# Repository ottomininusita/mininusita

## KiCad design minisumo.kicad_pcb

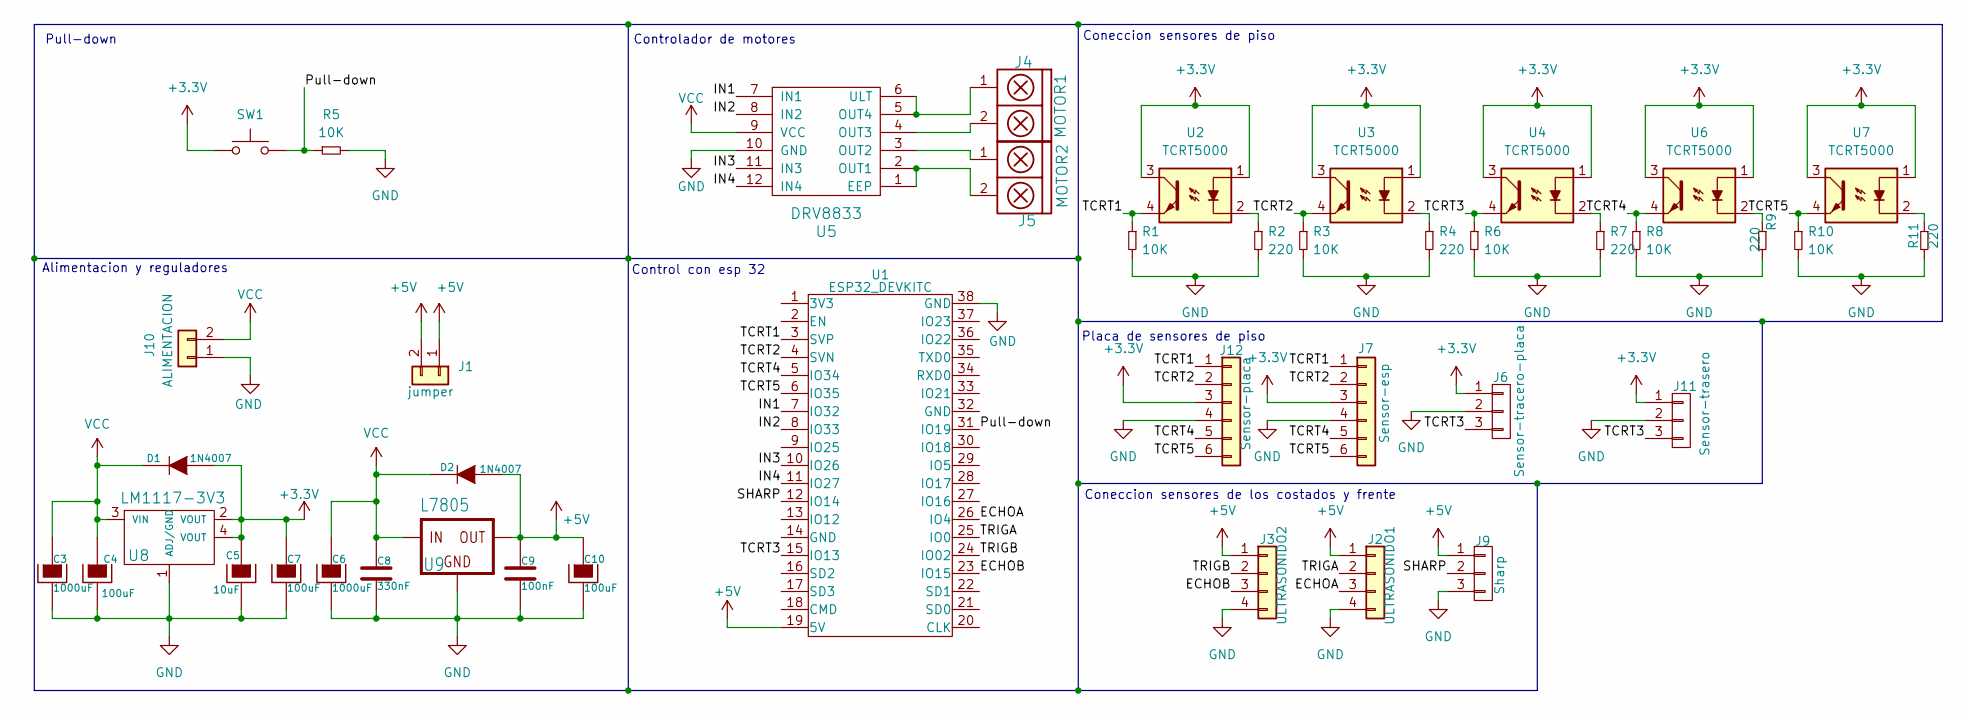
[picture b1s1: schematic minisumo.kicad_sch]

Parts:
C3, C6: 1000uF; CAP_ELEC_8x11.5mm
C4, C7, C10: 100uF; CP_Elec_6.3x5.4
C5: 10uF; CP_Elec_4x5.4
C8: 330nF; C_0805
C9: 100nF; C_0805
D1, D2: 1N4007; SOD80C
J1: jumper; Jumper
J2: ULTRASONIDO1; pin_strip_4
J3: ULTRASONIDO2; pin_strip_4
J4: MOTOR1; PinHeader_1x02_P2.54mm_Vertical
J5: MOTOR2; PinHeader_1x02_P2.54mm_Vertical
J6: Sensor-tracero-placa; Pin_Header_3
J7: Sensor-esp; Pin_Header_6
J9: Sharp; Pin_Header_3
J10: ALIMENTACION; Jumper
J11: Sensor-trasero; Pin_Header_3
J12: Sensor-placa; Pin_Header_6
R1, R3, R6, R8, R10: 10K; R_1206
R2, R4, R7, R9, R11: 220; R_1206
R5: 10K; RES0.3
SW1: SW_Push; Pulsador_SMD_2_BAJO
U1: ESP32_DEVKITC; ESP32S
U2, U3, U4, U6, U7: TCRT5000
U5: DRV8833; drv8833b
U8: LM1117-3V3; TO261AA-LM1117
U9: L7805; D2PAK

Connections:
+3.3V: C5.1, C7.1, D1.1 (A), J6.1, J7.3, J11.1, J12.3, SW1.1, U2.1, U2.3, U3.1, U3.3, U4.1, U4.3, U6.1, U6.3, U7.1, U7.3, U8.2 (VOUT), U8.4 (VOUT)
+5V: C9.1, C10.1, D2.1 (A), J1.1, J1.2, J2.1, J3.1, J9.1, U1.19 (5V), U9.3 (VOUT)
/ECHOA: J2.3, U1.26 (IO4)
/ECHOB: J3.3, U1.23 (IO15)
/IN1: U1.7 (IO32), U5.7 (IN1)
/IN2: U1.8 (IO33), U5.8 (IN2)
/IN3: U1.10 (IO26), U5.11 (IN3)
/IN4: U1.11 (IO27), U5.12 (IN4)
/Pull-down: R5.1, SW1.2, U1.31 (IO19)
/SHARP: J9.2, U1.12 (IO14)
/TCRT1: J7.1, J12.1, R1.1, U1.3 (SVP), U2.4
/TCRT2: J7.2, J12.2, R3.1, U1.4 (SVN), U3.4
/TCRT3: J6.3, J11.3, R6.1, U1.15 (IO13), U4.4
/TCRT4: J7.5, J12.5, R8.1, U1.5 (IO34), U6.4
/TCRT5: J7.6, J12.6, R10.1, U1.6 (IO35), U7.4
/TRIGA: J2.2, U1.25 (IO0)
/TRIGB: J3.2, U1.24 (IO02)
GND: C3.2, C4.2, C5.2, C6.2, C7.2, C8.2, C9.2, C10.2, J2.4, J3.4, J6.2, J7.4, J9.3, J10.1, J11.2, J12.4, R1.2, R2.2, R3.2, R4.2, R5.2, R6.2, R7.2, R8.2, R9.2, R10.2, R11.2, U1.38 (GND), U5.10 (GND), U8.1 (ADJ/GND), U9.2 (GND)
unnamed: R2.1, U2.2
unnamed: R4.1, U3.2
unnamed: R7.1, U4.2
unnamed: R9.1, U6.2
unnamed: R11.1, U7.2
unnamed: J5.2, U5.1 (EEP), U5.2 (OUT1)
unnamed: J5.1, U5.3 (OUT2)
unnamed: J4.2, U5.4 (OUT3)
unnamed: J4.1, U5.5 (OUT4), U5.6 (ULT)
VCC: C3.1, C4.1, C6.1, C8.1, D1.2 (K), D2.2 (K), J10.2, U5.9 (VCC), U8.3 (VIN), U9.1 (VIN)

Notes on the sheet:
Alimentacion y reguladores
Controlador de motores
Pull-down
Control con esp 32
Coneccion sensores de los costados y frente
Placa de sensores de piso
Coneccion sensores de piso

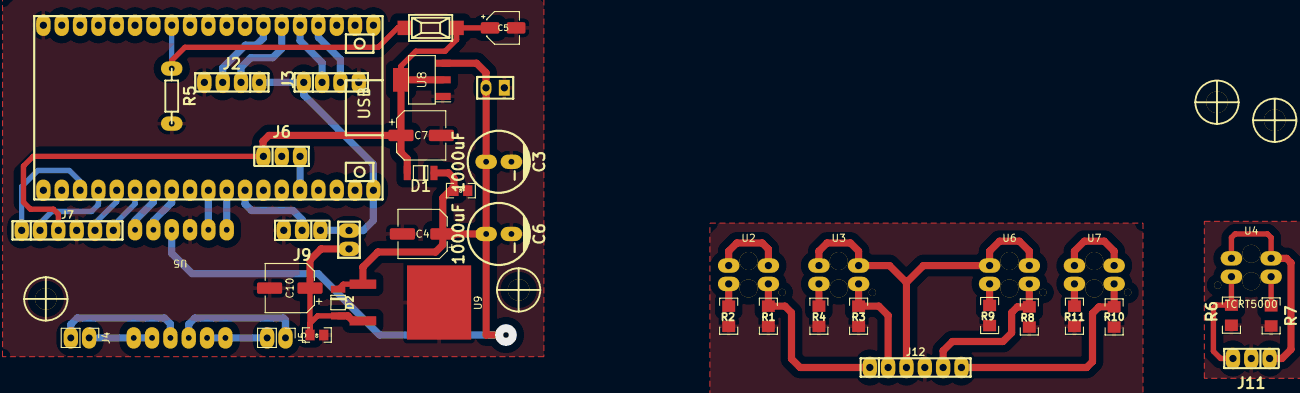
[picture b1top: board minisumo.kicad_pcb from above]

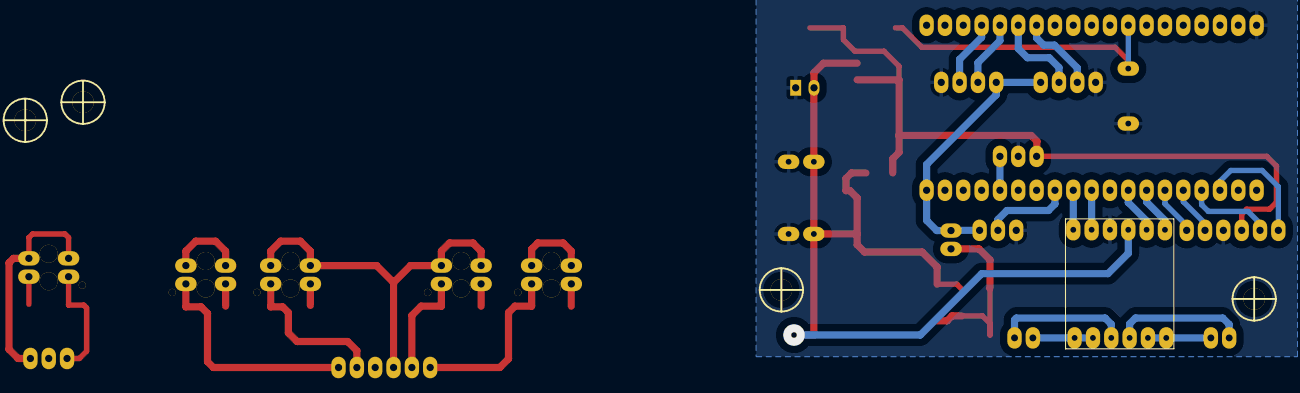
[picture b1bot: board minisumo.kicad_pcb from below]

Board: 2 copper layers, 46 parts (5 on the bottom side), 28 nets.

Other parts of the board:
hole_3mm, hole_3mm#2, hole_3mm#3, hole_3mm#4: VAL**; hole_3mm

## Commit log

2024-09-17 Create 3D
2024-09-17 Update 3D
2024-09-18 Create 3DD
    DISEÑOS
2024-09-18 Create diseños 3d
